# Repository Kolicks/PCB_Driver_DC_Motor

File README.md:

# ⚡ PCB_DC_Driver
**Single DC Motor Driver with H-Bridge Architecture**

---

<p align="center">
  
</p>

---

## 📘 Overview
**PCB_DC_Driver** is a theoretical yet practical design for a **DC motor driver** built around an **H-Bridge architecture** using dedicated gate drivers.  
The project focuses on achieving an efficient, compact, and manufacturable design while following **Design for Assembly (DFA)** and **Design for Manufacturing (DFM)** principles.

<p align="center">
  
  <br>
  <em>3D render of the finished PCB_DC_Driver board</em>
</p>

---

## ⚙️ General Information
- Theoretical **simple DC driver** implementing an **H-Bridge** with gate drivers.  
- Designed with **DFA** considerations to optimize ease of assembly and production workflow.  
- Built on **2 layers**, using **standard FR4 (TG135)** core and prepreg stackup, **1.6 mm thickness**.  

<p align="center">
  
  <br>
  <em>Full schematic diagram of the PCB_DC_Driver (KiCad 9)</em>
</p>

---

## 🔧 Characteristics
- Controls **one DC motor** with full H-Bridge operation.  
- Supports up to **10 A continuous current**, limited by the gate drivers and onboard fuse.  
- Operates at **24 VDC** nominal input voltage.  
- **All high-current power lanes routed on the top layer** to simplify current flow and reduce noise.  
- **All components placed on the top side**, enabling a **two-step DFA process**:  
  - Reflow soldering for SMD components.  
  - Wave soldering for through-hole parts.  
- **DFM-compliant design**:  
  - Includes multiple **mounting holes**.  
  - **Maximum PCB size:** 100 × 100 mm (optimized for **JLCPCB**).  
  - **Surface finish:** HASL (with lead).  
  - **Tented vias** for protection and manufacturing consistency.  
- **Optimized gate loop design:**  
  - Gate drivers positioned close to MOSFETs to minimize loop inductance.  
  - Bottom ground layer cleared in high-current paths to ensure controlled current direction and reduce EMI/EMC issues.
- **Space between MOSFET**: For a 20x15 Mounted radiators space. 
- **Microcontroller:** Reused **STM32F030K6T6** from previous projects for convenience, reusability, and familiarity with existing firmware.

<p align="center">
  
  <br>
  <em>Top layer routing and overall PCB layout (KiCad 9)</em>
</p>

---

## ⚠️ Design Notes
- Power paths designed with proper copper width for 10 A continuous load capability.  
- Ground and power planes isolated to improve switching behavior and minimize noise coupling.  
- Routing and layout optimized for **EMI/EMC performance**.  
- Designed for **expandability**, allowing integration of PWM control, fault sensing, or current feedback in future iterations.  

---

## 🧩 Repository Structure
PCB_DC_Driver/

├── schematic/ # KiCad schematic files

├── pcb_layout/ # KiCad PCB layout files

├── gerbers/ # Gerber fabrication files

├── images/ # Rendered visuals (3D, SCH, PCB)

├── LICENSE # Hardware license (CERN-OHL-P v2.0)

└── README.md # Project documentation

---

## 📜 License
This hardware design is released under the **CERN Open Hardware License v2 – Permissive (CERN-OHL-P-2.0)**.  
You are free to use, modify, and distribute this design, provided that:
- The license is included with redistributions.
- Proper credit is given to the original author.

More info: https://cern-ohl.web.cern.ch/

---

## 👤 Author
**Project:** PCB_DC_Driver  
**Author:** [Kolicks]  
**Toolchain:** KiCad 9  
**Version:** 9.0  

---

## 🧱 Future Improvements

- **Thermal Management:**  
  - Integrate larger or multi-via thermal pads under the MOSFETs and drivers to enhance heat dissipation.  
  - Evaluate adding **heatsinks or via arrays** for improved performance under sustained 10 A load.  

- **Power Optimization:**  
  - Consider using **2 oz copper** for better current capacity and lower resistive losses.  
  - Evaluate a **four-layer design** with dedicated GND and VCC planes for improved EMI and power distribution.  

- **Protection & Monitoring:**  
  - Add **current sense resistors** and amplifiers for real-time feedback and overcurrent protection.  
  - Implement **reverse polarity**, **undervoltage**, and **thermal shutdown** protection.  
  - Include **snubber or flyback diode networks** to suppress switching transients.  

- **Diagnostics & User Interface:**  
  - Integrate **LED indicators** for power, fault, and enable states.  
  - Add **test points** for gate and driver outputs for easier debugging and measurement.  

- **Control Enhancements:**  
  - Implement **PWM-based speed and direction control** in firmware.  
  - Add **UART or CAN communication** for remote control and telemetry.  
  - Enable **firmware upgradability** via USB or serial interface.  

- **Mechanical & Assembly Improvements:**  
  - Add **mounting supports for heatsinks or enclosures**.  
  - Improve **silkscreen labeling** for connectors and test points.  
  - Optimize **component placement** for serviceability and rework.  

---

⭐ *If you find this project useful or educational, please consider starring the repository and sharing feedback!*

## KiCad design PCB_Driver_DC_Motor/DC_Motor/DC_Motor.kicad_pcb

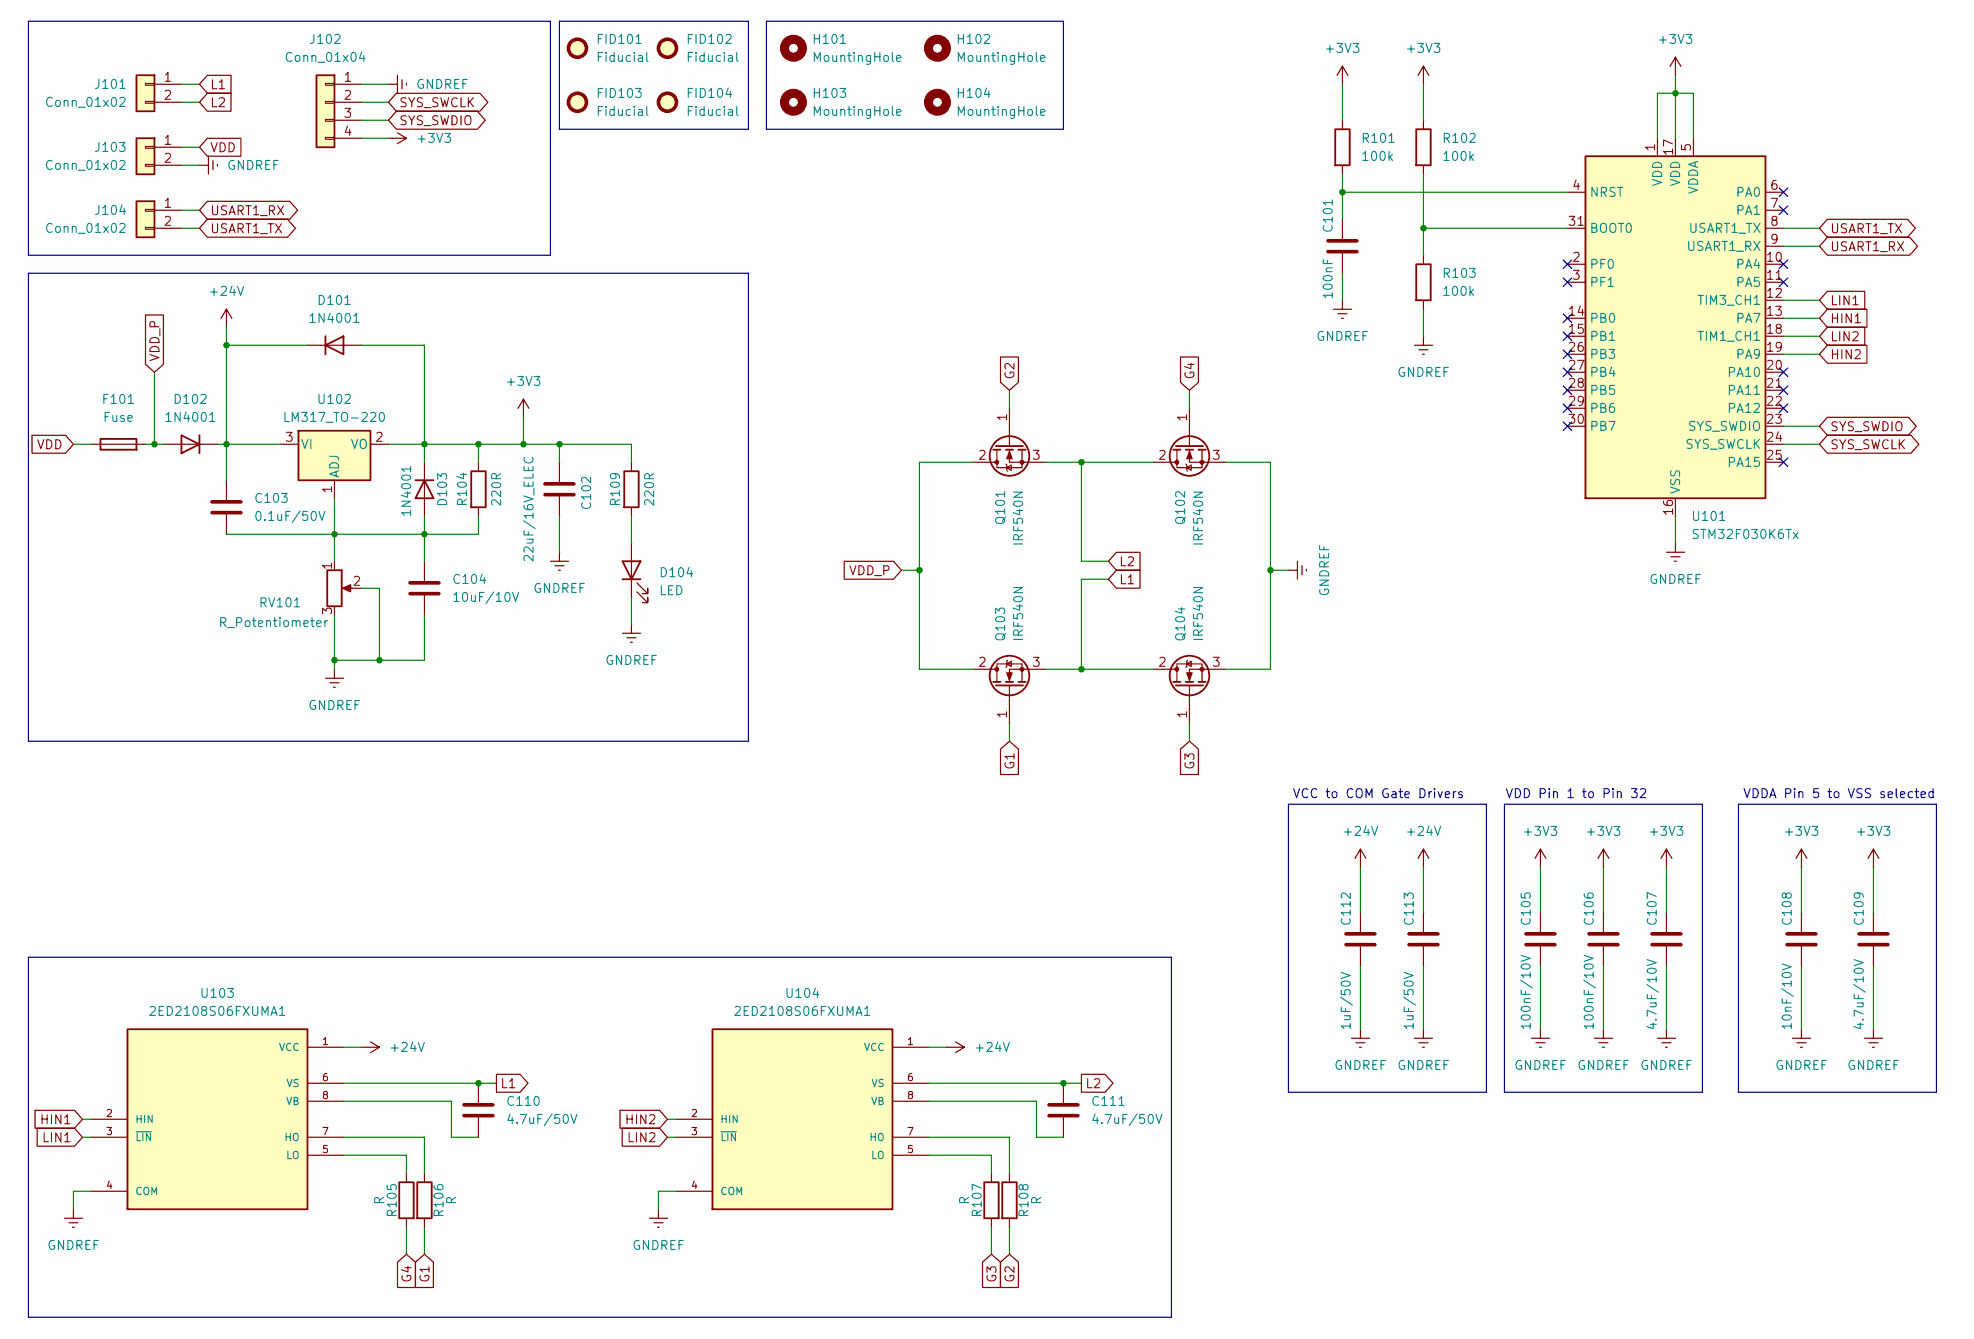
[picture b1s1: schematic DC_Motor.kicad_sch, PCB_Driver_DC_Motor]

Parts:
C101: 100nF; C_0603_1608Metric
C102: 22uF/16V_ELEC; C_Elec_4x5.4
C103: 0.1uF/50V; C_0603_1608Metric_Pad1.08x0.95mm_HandSolder
C104: 10uF/10V; C_0603_1608Metric_Pad1.08x0.95mm_HandSolder
C105, C106: 100nF/10V; C_0603_1608Metric
C107, C109: 4.7uF/10V; C_0603_1608Metric
C108: 10nF/10V; C_0603_1608Metric
C110, C111: 4.7uF/50V; C_0603_1608Metric_Pad1.08x0.95mm_HandSolder
C112, C113: 1uF/50V; C_0603_1608Metric
D101, D102, D103: 1N4001; D_SMA
D104: LED; LED_0603_1608Metric_Pad1.05x0.95mm_HandSolder
F101: Fuse; Fuseholder_Cylinder-6.3x32mm_Schurter_0031-8002_Horizontal_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
FID101, FID102, FID103, FID104: Fiducial; Fiducial_1mm_Mask3mm
H101, H102, H103, H104: MountingHole; MountingHole_5.3mm_M5_ISO14580
J101, J103, J104: Conn_01x02; PhoenixContact_MSTBVA_2,5_2-G-5,08_1x02_P5.08mm_Vertical
J102: Conn_01x04; Molex_KK-254_AE-6410-04A_1x04_P2.54mm_Vertical
Q101, Q102, Q103, Q104: IRF540N; TO-220-3_Vertical
R101, R102, R103: 100k; R_0603_1608Metric
R104, R109: 220R; R_0201_0603Metric_Pad0.64x0.40mm_HandSolder
R105, R106, R107, R108: R; R_0201_0603Metric_Pad0.64x0.40mm_HandSolder
RV101: R_Potentiometer; Potentiometer_Piher_PT-10-V10_Vertical
U101: STM32F030K6Tx; LQFP-32_7x7mm_P0.8mm
U102: LM317_TO-220; TO-220-3_Vertical
U103, U104: 2ED2108S06FXUMA1; SOIC127P600X172-8N; PARTREV 2.20

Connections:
+3V3: C102.1, C105.1, C106.1, C107.1, C108.1, C109.1, D101.2 (A), D103.1 (K), J102.4, R101.1, R102.1, R104.1, R109.1, U101.1 (VDD), U101.5 (VDDA), U101.17 (VDD), U102.2 (VO)
+24V: C103.1, C112.1, C113.1, D101.1 (K), D102.1 (K), U102.3 (VI), U103.1 (VCC), U104.1 (VCC)
G1: Q103.1 (G), R106.2
G2: Q101.1 (G), R108.2
G3: Q104.1 (G), R107.2
G4: Q102.1 (G), R105.2
GNDREF: C101.2, C102.2, C104.2, C105.2, C106.2, C107.2, C108.2, C109.2, C112.2, C113.2, D104.1 (K), J102.1, J103.2, Q102.3 (S), Q104.3 (S), R103.2, RV101.2, RV101.3, U101.16 (VSS), U101.32 (VSS), U103.4 (COM), U104.4 (COM)
HIN1: U101.13 (PA7), U103.2 (HIN)
HIN2: U101.19 (PA9), U104.2 (HIN)
L1: C110.1, J101.1, Q103.3 (S), Q104.2 (D), U103.6 (VS)
L2: C111.1, J101.2, Q101.3 (S), Q102.2 (D), U104.6 (VS)
LIN1: U101.12 (TIM3_CH1), U103.3 (~LIN)
LIN2: U101.18 (TIM1_CH1), U104.3 (~LIN)
unnamed: C103.2, C104.1, D103.2 (A), R104.2, RV101.1, U102.1 (ADJ)
unnamed: D104.2 (A), R109.2
unnamed: R102.2, R103.1, U101.31 (BOOT0)
unnamed: C101.1, R101.2, U101.4 (NRST)
unnamed: R106.1, U103.7 (HO)
unnamed: R105.1, U103.5 (LO)
unnamed: C110.2, U103.8 (VB)
unnamed: R108.1, U104.7 (HO)
unnamed: R107.1, U104.5 (LO)
unnamed: C111.2, U104.8 (VB)
SYS_SWCLK: J102.2, U101.24 (SYS_SWCLK)
SYS_SWDIO: J102.3, U101.23 (SYS_SWDIO)
USART1_RX: J104.1, U101.9 (USART1_RX)
USART1_TX: J104.2, U101.8 (USART1_TX)
VDD: F101.1, J103.1
VDD_P: D102.2 (A), F101.2, Q101.2 (D), Q103.2 (D)

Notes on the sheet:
VDD Pin 1 to Pin 32
VCC to COM Gate Drivers
VDDA Pin 5 to VSS selected

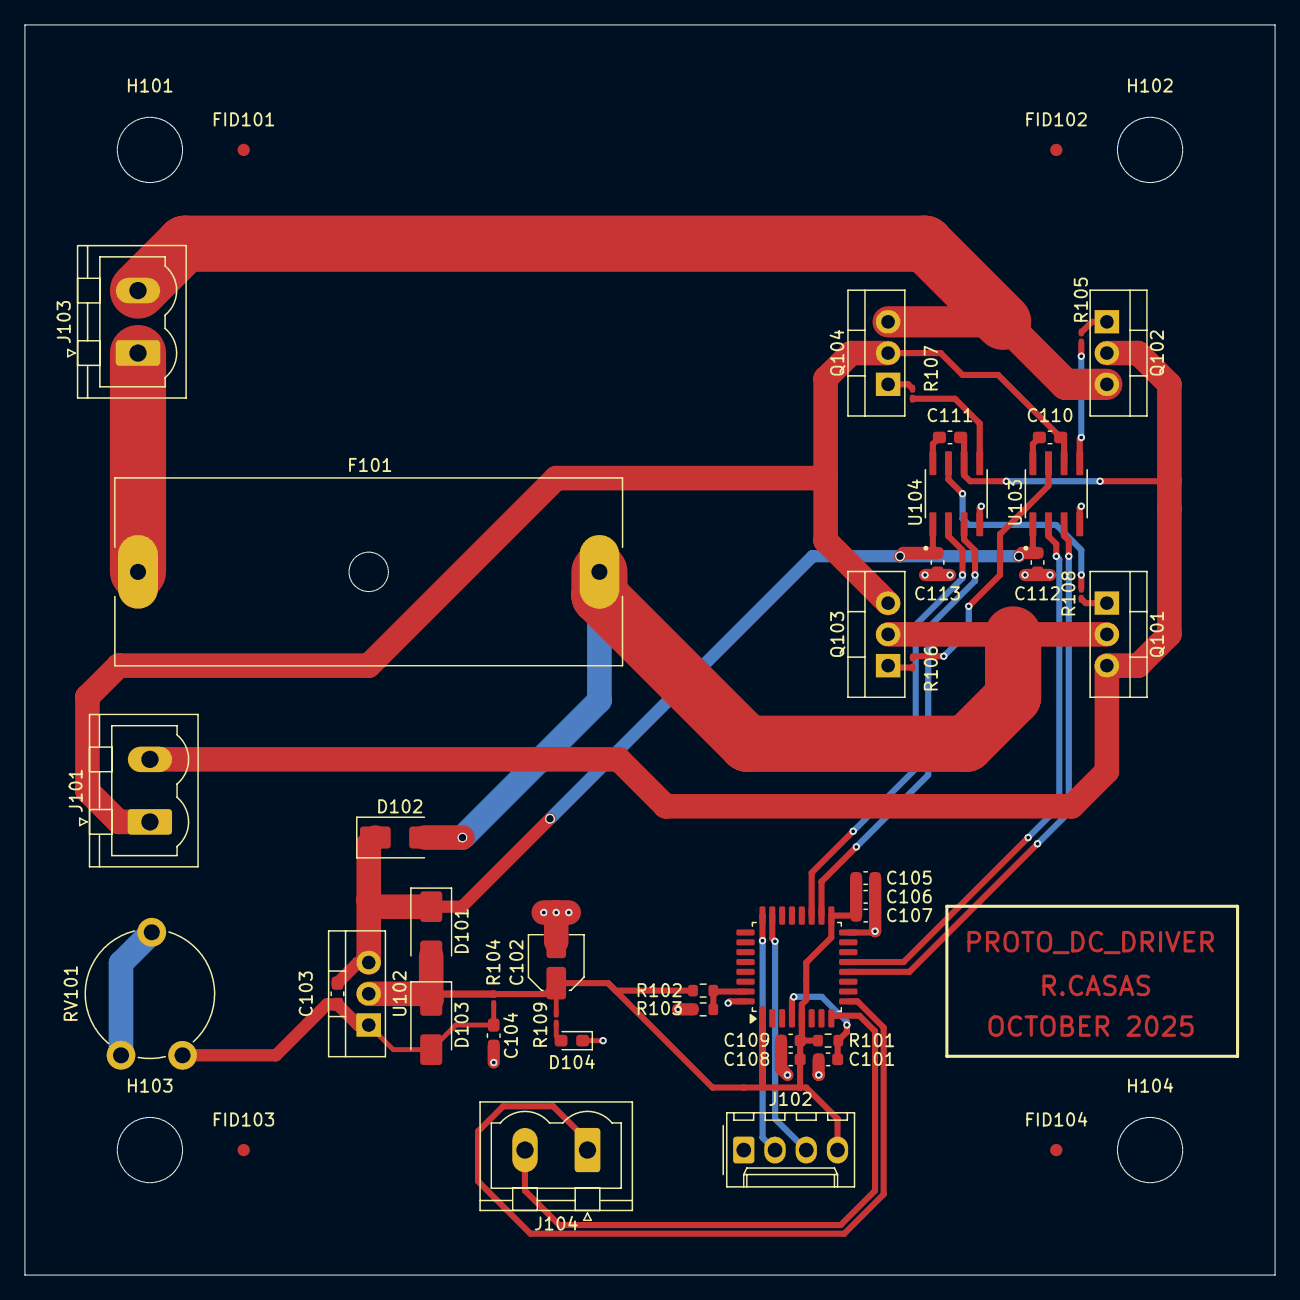
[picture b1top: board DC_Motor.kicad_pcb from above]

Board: 2 copper layers, 101.6 x 101.6 mm, 48 parts (0 on the bottom side), 29 nets.

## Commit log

2025-10-17 Update README with MOSFET spacing information
    Added a note about the space between MOSFETs for mounted radiators.
2025-10-17 Fix image source path in README.md
2025-10-17 Update PCB image source in README
2025-10-28 Update README with repository structure and improvements
    Added repository structure and future improvement suggestions.
